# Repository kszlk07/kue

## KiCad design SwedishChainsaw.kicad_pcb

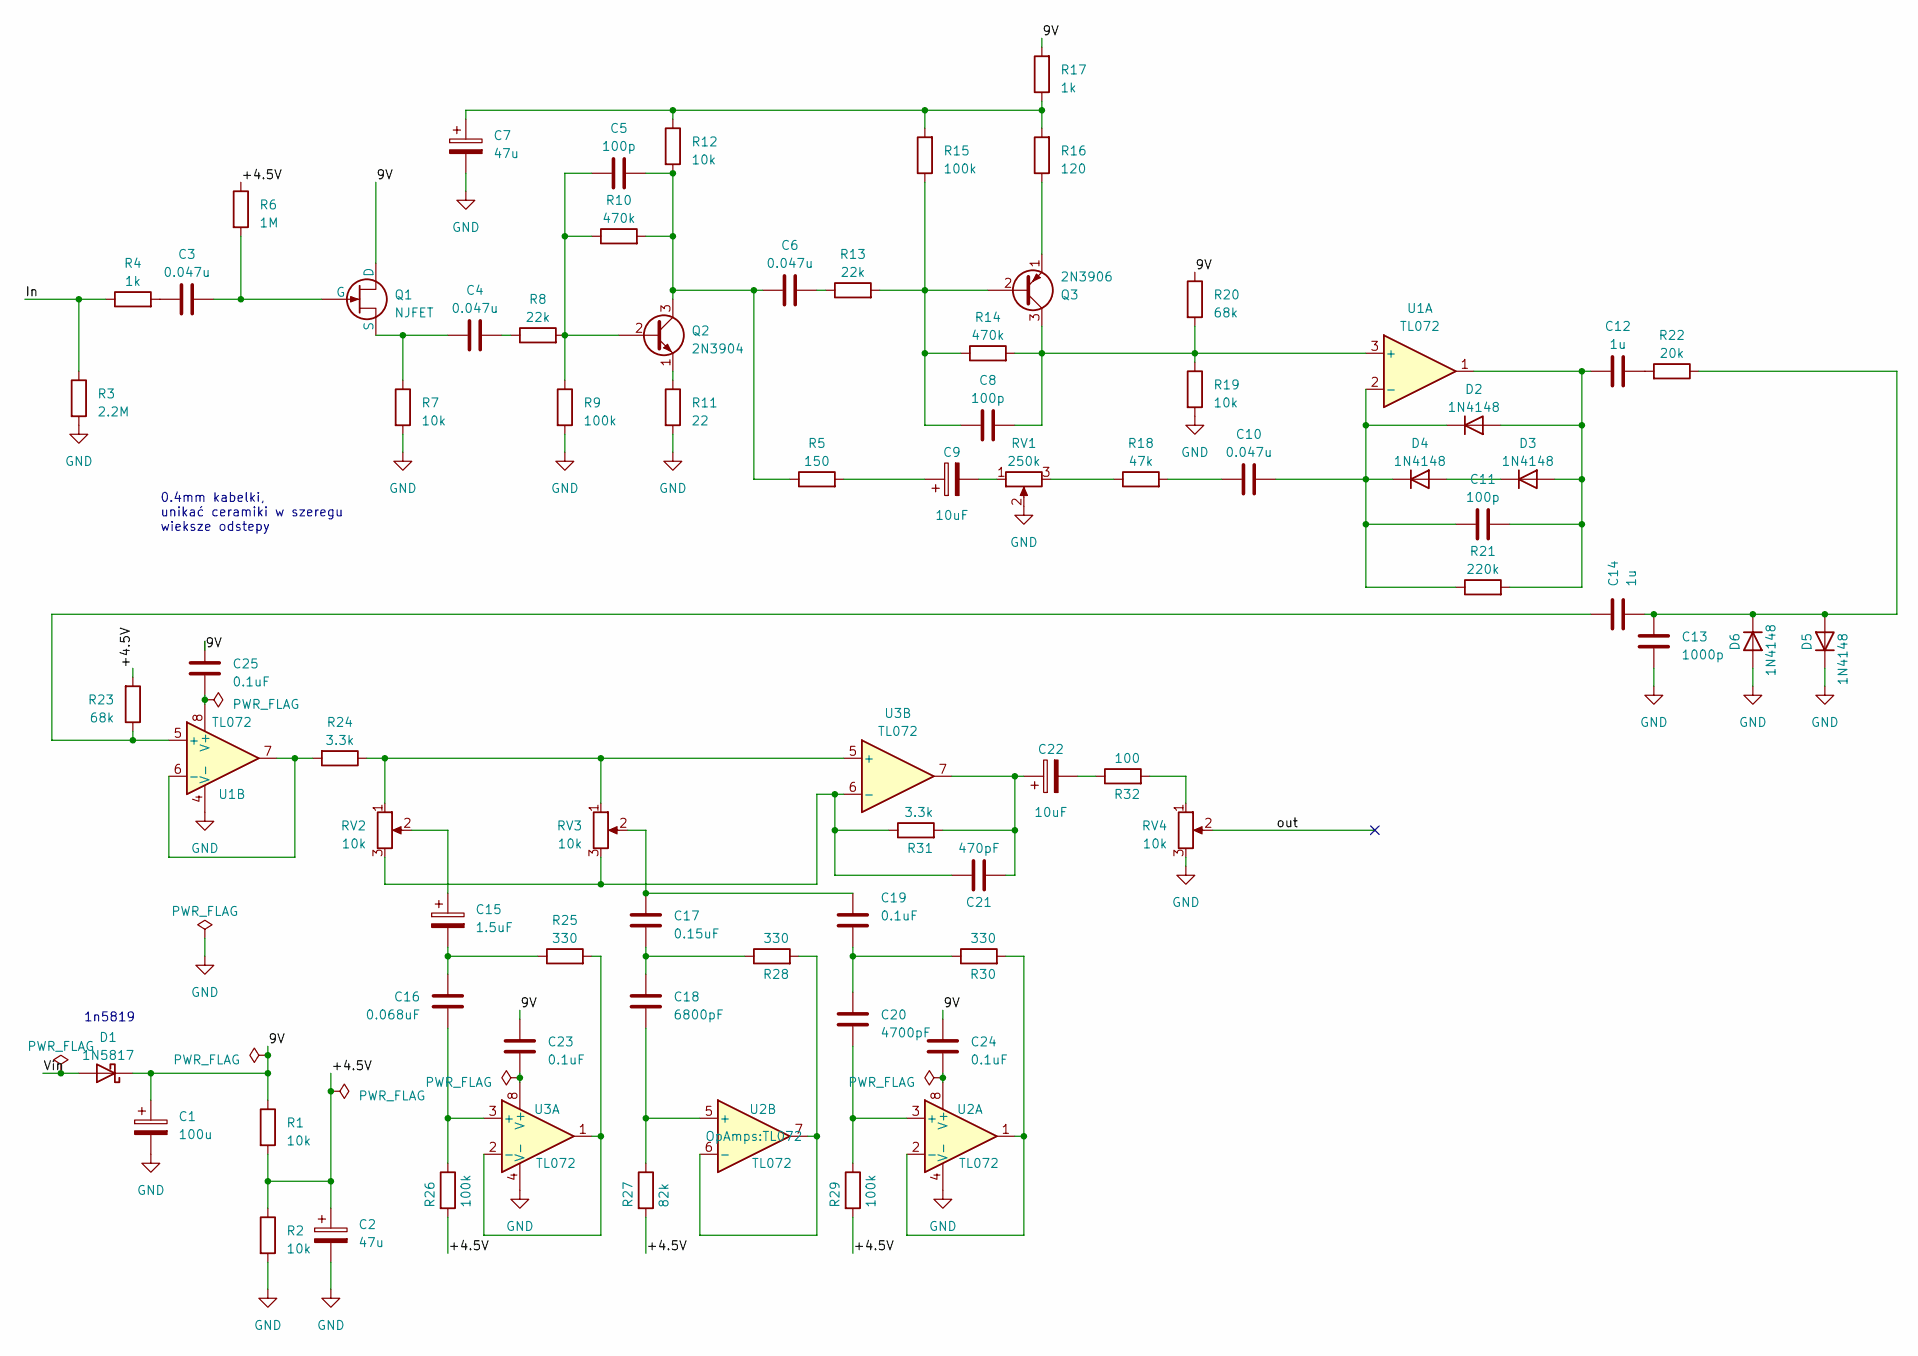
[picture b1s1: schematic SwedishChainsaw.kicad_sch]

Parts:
C1: 100u; CP_Radial_D6.3mm_P2.50mm
C2, C7: 47u; CP_Radial_D5.0mm_P2.50mm
C3, C4, C6, C10: 0.047u; C_Rect_L7.2mm_W3.0mm_P5.00mm_FKS2_FKP2_MKS2_MKP2
C5, C8, C11: 100p; C_Disc_D4.3mm_W1.9mm_P5.00mm
C9, C22: 10uF; CP_Radial_D5.0mm_P2.00mm
C12, C14: 1u; C_Disc_D7.5mm_W5.0mm_P5.00mm
C13: 1000p; C_Disc_D4.7mm_W2.5mm_P5.00mm
C15: 1.5uF; CP_Radial_D4.0mm_P1.50mm
C16: 0.068uF; C_Disc_D5.1mm_W3.2mm_P5.00mm
C17: 0.15uF; C_Disc_D5.1mm_W3.2mm_P5.00mm
C18: 6800pF; C_Disc_D6.0mm_W4.4mm_P5.00mm
C19, C23, C24: 0.1uF; C_Disc_D5.0mm_W2.5mm_P5.00mm
C20: 4700pF; C_Disc_D6.0mm_W4.4mm_P5.00mm
C21: 470pF; C_Disc_D4.3mm_W1.9mm_P5.00mm
C25: 0.1uF; C_Disc_D5.1mm_W3.2mm_P5.00mm
D1: 1N5817; D_DO-41_SOD81_P10.16mm_Horizontal
D2, D3, D4, D5, D6: 1N4148; D_A-405_P7.62mm_Horizontal
Q1: NJFET; TO-92_Inline_Wide
Q2: 2N3904; TO-92_Inline_Wide
Q3: 2N3906; TO-92_Inline_Wide
R1, R2, R7, R12, R19: 10k; R_Axial_DIN0204_L3.6mm_D1.6mm_P5.08mm_Horizontal
R3: 2.2M; R_Axial_DIN0204_L3.6mm_D1.6mm_P5.08mm_Horizontal
R4, R17: 1k; R_Axial_DIN0204_L3.6mm_D1.6mm_P5.08mm_Horizontal
R5: 150; R_Axial_DIN0204_L3.6mm_D1.6mm_P7.62mm_Horizontal
R6: 1M; R_Axial_DIN0204_L3.6mm_D1.6mm_P5.08mm_Horizontal
R8, R13: 22k; R_Axial_DIN0204_L3.6mm_D1.6mm_P7.62mm_Horizontal
R9, R15, R26, R29: 100k; R_Axial_DIN0204_L3.6mm_D1.6mm_P5.08mm_Horizontal
R10, R14: 470k; R_Axial_DIN0204_L3.6mm_D1.6mm_P5.08mm_Horizontal
R11: 22; R_Axial_DIN0204_L3.6mm_D1.6mm_P7.62mm_Horizontal
R16: 120; R_Axial_DIN0204_L3.6mm_D1.6mm_P7.62mm_Horizontal
R18: 47k; R_Axial_DIN0204_L3.6mm_D1.6mm_P5.08mm_Horizontal
R20, R23: 68k; R_Axial_DIN0204_L3.6mm_D1.6mm_P7.62mm_Horizontal
R21: 220k; R_Axial_DIN0204_L3.6mm_D1.6mm_P5.08mm_Horizontal
R22: 20k; R_Axial_DIN0204_L3.6mm_D1.6mm_P5.08mm_Horizontal
R24, R31: 3.3k; R_Axial_DIN0204_L3.6mm_D1.6mm_P7.62mm_Horizontal
R25, R28, R30: 330; R_Axial_DIN0204_L3.6mm_D1.6mm_P5.08mm_Horizontal
R27: 82k; R_Axial_DIN0204_L3.6mm_D1.6mm_P5.08mm_Horizontal
R32: 100; R_Axial_DIN0204_L3.6mm_D1.6mm_P5.08mm_Horizontal
RV1: 250k; Potentiometer_Alpha_RD901F-40-00D_Single_Vertical_CircularH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
RV2, RV3, RV4: 10k; Potentiometer_Alpha_RD901F-40-00D_Single_Vertical_CircularH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
U1, U2, U3: TL072

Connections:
/9V: C1.1, C23.1, C24.1, C25.1, D1.1 (K), Q1.1 (D), R1.1, R17.2, R20.1
/+4.5V: C2.1, R1.2, R2.1, R6.1, R23.2, R26.2, R27.2, R29.2
/In: R3.1, R4.1; also elsewhere on the board
/Vin: D1.2 (A); also elsewhere on the board
/out: RV4.2; also elsewhere on the board
GND: C1.2, C2.2, C7.2, C13.1, D5.1 (K), D6.2 (A), R2.2, R3.2, R7.2, R9.2, R11.2, R19.2, RV1.2, RV4.3, U1.4 (V-), U2.4 (V-), U3.4 (V-); also elsewhere on the board
unnamed: C3.1, R4.2
unnamed: C4.2, R8.1
unnamed: C6.2, R13.1
unnamed: C7.1, R12.1, R15.2, R16.2, R17.1
unnamed: C9.1, R5.2
unnamed: C9.2, RV1.1
unnamed: C10.1, R18.2
unnamed: C12.2, R22.2
unnamed: C15.1, RV2.2
unnamed: C15.2, C16.2, R25.1
unnamed: C17.1, C18.2, R28.1
unnamed: C17.2, C19.2, RV3.2
unnamed: C19.1, C20.2, R30.1
unnamed: C21.1, C22.1, R31.2, U3.7
unnamed: C22.2, R32.1
unnamed: C11.2, C12.1, D2.2 (A), D3.2 (A), R21.2, U1.1
unnamed: C10.2, C11.1, D2.1 (K), D4.1 (K), R21.1, U1.2 (-)
unnamed: D3.1 (K), D4.2 (A)
unnamed: C13.2, C14.1, D5.2 (A), D6.1 (K), R22.1
unnamed: C3.2, Q1.2 (G), R6.2
unnamed: C4.1, Q1.3 (S), R7.1
unnamed: C5.1, Q2.2 (B), R8.2, R9.1, R10.1
unnamed: C5.2, C6.1, Q2.3 (C), R5.1, R10.2, R12.2
unnamed: Q2.1 (E), R11.1
unnamed: C8.1, Q3.2 (B), R13.2, R14.1, R15.1
unnamed: C8.2, Q3.3 (C), R14.2, R19.1, R20.2, U1.3 (+)
unnamed: Q3.1 (E), R16.1
unnamed: R18.1, RV1.3
unnamed: R32.2, RV4.1
unnamed: C14.2, R23.1, U1.5 (+)
unnamed: R24.2, U1.6 (-), U1.7
unnamed: C25.2, U1.8 (V+)
unnamed: C20.1, R29.1, U2.3 (+)
unnamed: R30.2, U2.1, U2.2 (-)
unnamed: C18.1, R27.1, U2.5 (+)
unnamed: R28.2, U2.6 (-), U2.7
unnamed: C24.2, U2.8 (V+)
unnamed: C16.1, R26.1, U3.3 (+)
unnamed: R25.2, U3.1, U3.2 (-)
unnamed: R24.1, RV2.1, RV3.1, U3.5 (+)
unnamed: C21.2, R31.1, RV2.3, RV3.3, U3.6 (-)
unnamed: C23.2, U3.8 (V+)

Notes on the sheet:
1n5819
0.4mm kabelki, unikać ceramiki w szeregu wieksze odstepy

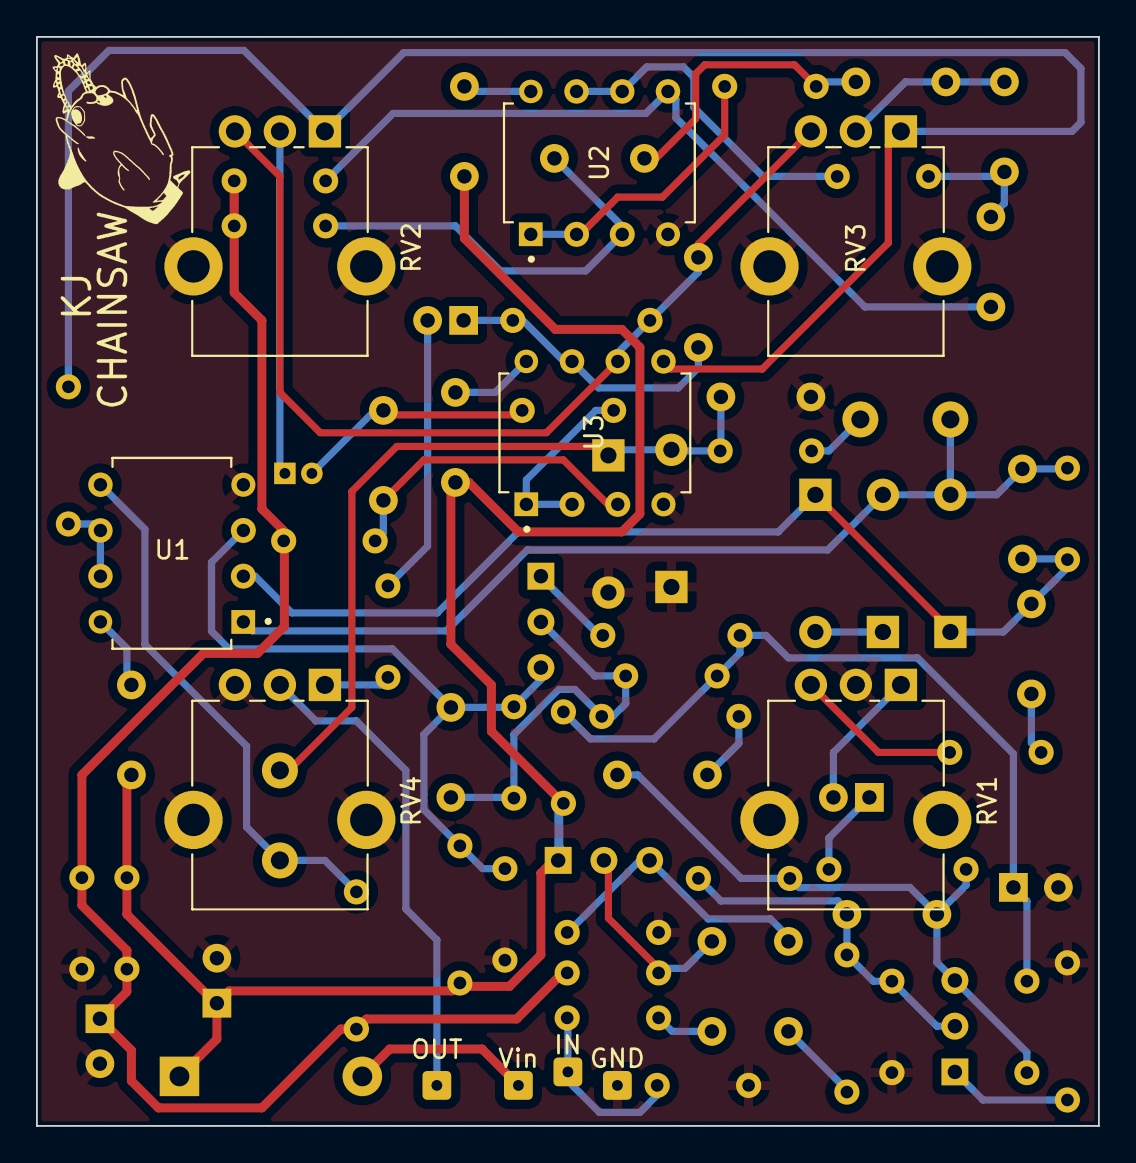
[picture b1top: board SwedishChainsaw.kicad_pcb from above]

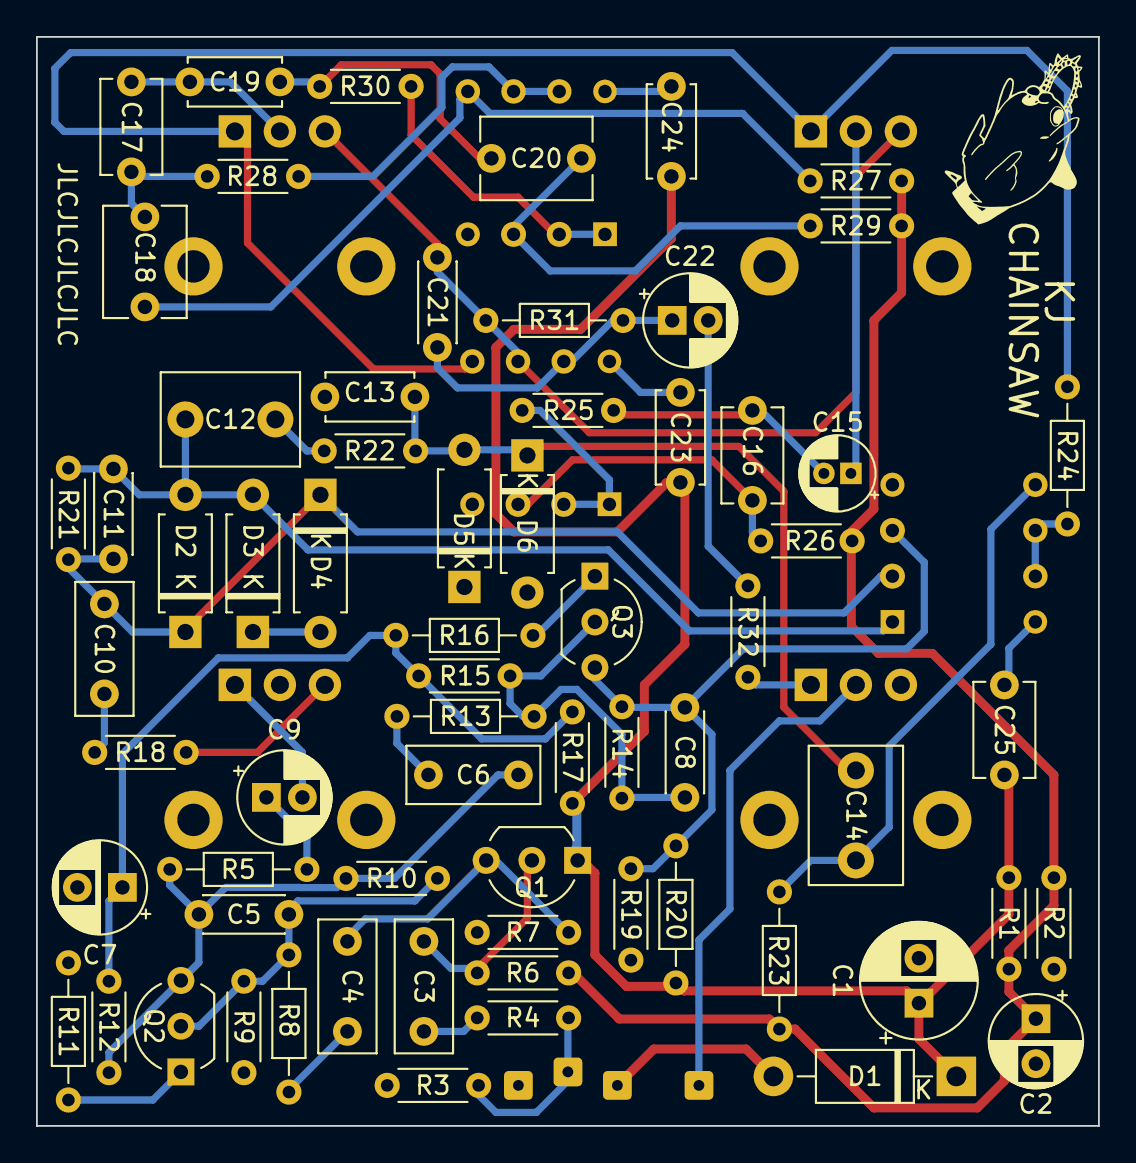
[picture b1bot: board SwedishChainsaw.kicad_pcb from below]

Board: 2 copper layers, 59.0 x 60.5 mm, 77 parts (66 on the bottom side), 48 nets.

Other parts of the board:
GND: SolderWire-0.1sqmm_1x01_D0.4mm_OD1mm
IN: SolderWire-0.1sqmm_1x01_D0.4mm_OD1mm
OUT: SolderWire-0.1sqmm_1x01_D0.4mm_OD1mm
Vin: SolderWire-0.1sqmm_1x01_D0.4mm_OD1mm

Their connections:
/In: IN.1; also elsewhere on the board
/Vin: Vin.1; also elsewhere on the board
/out: OUT.1; also elsewhere on the board
GND: GND.1; also elsewhere on the board

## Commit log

2023-05-18 final
